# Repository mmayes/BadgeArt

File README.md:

# BadgeArt
Resources for learning how to make PCB badge art

### Element14 text tutorials
* [KiCad 6 - Importing Complex Board Outlines as Vector Graphics](https://community.element14.com/members-area/b/blog/posts/kicad-6---importing-complex-board-outlines-as-vector-graphics)
* [KiCad 6 - Adding Logos and Graphics to a Silkscreen](https://community.element14.com/members-area/b/blog/posts/kicad-6---adding-logos-and-graphics-to-a-silkscreen)
* [KiCad 6 - Importing Complex Board Outlines as Vector Graphics](https://community.element14.com/members-area/b/blog/posts/kicad-6---importing-complex-board-outlines-as-vector-graphics)
* [KiCad 6 - Creating PCB Art and Badges](https://community.element14.com/members-area/b/blog/posts/kicad-6---creating-pcb-art-and-badges)
* [Rosie Learns to Solder](https://community.element14.com/members-area/personalblogs/b/frank-milburn-s-blog/posts/rosie-learns-to-solder)

### Stuart Patterson video tutorials
* [Advanced PCB Graphics with KiCAD 6 and Inkscape](https://www.youtube.com/watch?v=zjnwlTgil4A)
* [Complex Edge Cuts in KiCAD 5.x with Inkscape](https://www.youtube.com/watch?v=rhqlP8CRct0)
* [DIY Rudolph Christmas Tree Ornament](https://www.youtube.com/watch?v=8iXEibNfG_s)

### TwinkleTwinkie tutorials
* [Understanding & Making PCB Art - DEF CON 27 (2019) HHV Talk](https://www.youtube.com/watch?v=Sbkvza8cKQE)
* [PCB Art is Pain](https://www.youtube.com/watch?v=5G-uHDRKI1k)

### Hackster tutorials
* [Design a SAO in KiCad](https://www.youtube.com/watch?v=bXg2j4ttgis)
* [Design a SAO in KiCad](https://www.hackster.io/glowascii/design-a-sh-tty-add-on-in-kicad-06350f)
* [PCB Art Workshop w/Andrew Sowa](https://www.youtube.com/watch?v=-QPkSICzRDk&t=0s)

### Other tutorials/examples
* [Negative Copper Art in KiCad](https://medium.com/the-bkpt/negative-copper-art-in-kicad-d9fae03d9996)
* [Creating Circuit Boards with KiCad 6](https://www.youtube.com/watch?v=5Be7XOMmPQE)
* [A TUTORIAL ON “MAKE NOISE” STYLE INDICATOR LIGHTS AND DESIGNING AN ILLUMINATED BLIND PLATE USING KICAD](https://www.threetom.com/news/a-tutorial-on-make-noise-style-indicator-lights-and-designing-an-illuminated-blind-plate-using-kicad/)
* [SAO PCB Art examples](https://github.com/LifeOnAFarm/SAO-PCB-Art)
* [Drawing PCBs with Inkscape Creating printed circuit board designs using Inkscape, SVG2Shenzhen, and KiCad](https://www.youtube.com/watch?v=xXRPw7ItMaM)
* [Making a PCB Badge for Hackaday Supercon!](https://www.youtube.com/watch?v=YqdBiOj8uXw)
* [A Practical Guide to Designing PCB Art](https://urish.medium.com/a-practical-guide-to-designing-pcb-art-b5aa22926a5c)

### JLPCB tutorials
* [How to generate Gerber and Drill files in KiCad 6](https://support.jlcpcb.com/article/194-how-to-generate-gerber-and-drill-files-in-kicad-6)
* [How to generate the BOM and Centroid file from KiCAD](https://support.jlcpcb.com/article/84-how-to-generate-the-bom-and-centroid-file-from-kicad)
* [KiCad 6 design rules using jlcpcb capabilities](https://www.youtube.com/watch?v=c00A5ZLMKI8)
* [JLCPCB - SMT Assembly with KiCad](https://www.youtube.com/watch?v=VejO8rDdhzo)

### SAO standard info
* [Simple Add-ons (SAO) v2](https://hackaday.io/project/175182-simple-add-ons-sao)
* [SAO v1.69bis standard](https://hackaday.io/project/52950-shitty-add-ons/log/159806-introducing-the-shitty-add-on-v169bis-standard)
* [INTRODUCING THE SHITTY ADD-ON V1.69BIS STANDARD](https://hackaday.com/2019/03/20/introducing-the-shitty-add-on-v1-69bis-standard/)

### Additional libraries/code
* [svg2shenzhen](https://github.com/twinkletwinkie/svg2shenzhen)
* [Inkscape Export Layers](https://github.com/jespino/inkscape-export-layers)
* [bitmap2component](https://github.com/KiCad/kicad-source-mirror/tree/master/bitmap2component)
* [svg2mod](https://github.com/svg2mod/svg2mod)
* [KiCAD JLCPCB tools](https://github.com/Bouni/kicad-jlcpcb-tools)

### Helpful pages for specific issues
* [How to include the canvas in an Inkscape PNG export?](https://graphicdesign.stackexchange.com/questions/137238/how-to-include-the-canvas-in-an-inkscape-png-export)
* [PRINTED CIRCUIT BOARD SURFACE FINISHES: ADVANTAGES AND DISADVANTAGES](https://www.epectec.com/articles/pcb-surface-finish-advantages-and-disadvantages.html)
* [How to Easily Invert Solder Mask Layer Graphics](https://forum.kicad.info/t/how-to-easily-invert-solder-mask-layer-graphics/13383)
* [How can I write text in solder mask?](https://forum.kicad.info/t/how-can-i-write-text-in-solder-mask/11587)
* [Halftone PCB art](http://ianrrees.github.io/2018/06/20/pcb-graphics-with-kicad-+-gimp.html)
* [Removing Solder Mask and Copper Fill YouTube video](https://youtu.be/TmriDK7Jpes)
* [Exporting Gerbers from the Beginner's Guide to KiCAD](https://learn.sparkfun.com/tutorials/beginners-guide-to-kicad/exporting-gerbers)

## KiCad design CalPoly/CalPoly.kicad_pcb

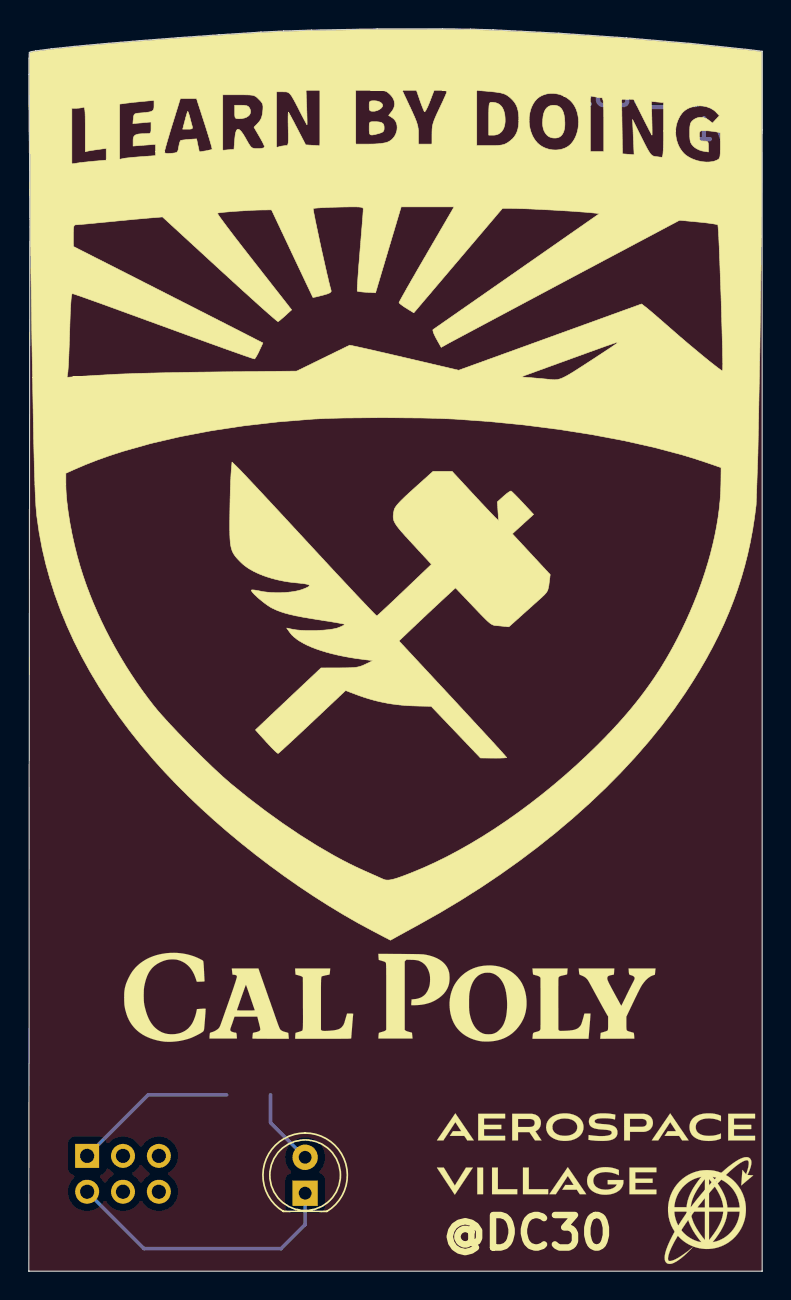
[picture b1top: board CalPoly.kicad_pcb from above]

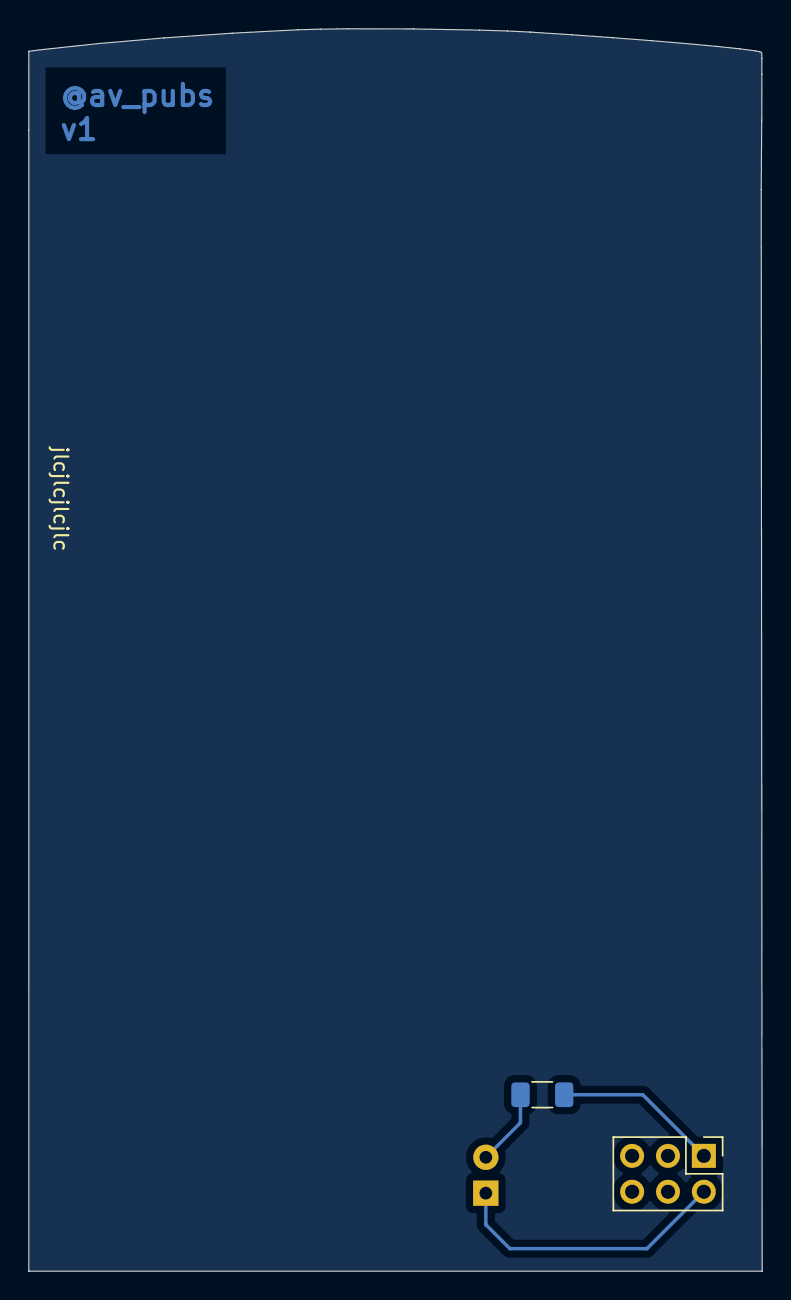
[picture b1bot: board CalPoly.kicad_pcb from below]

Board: 2 copper layers, 51.9 x 88.0 mm, 3 parts (2 on the bottom side), 3 nets.

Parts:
D1: LED; LED_D5.0mm
J1: Conn_02x03_Counter_Clockwise; PinHeader_2x03_P2.54mm_Vertical
R1: R; R_1206_3216Metric_Pad1.30x1.75mm_HandSolder

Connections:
unnamed: D1.2 (A), R1.1
unnamed: D1.1 (K), J1.2
unnamed: J1.1, R1.2

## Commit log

2022-05-04 First commit of links for learning badge art and SAOs
2022-05-04 Added link to github for KiCAD JLCPCB tools
2022-05-25 Added some links to address specific issues
2022-05-25 Added link for details on Halftone PCB Art
2022-07-02 AN225 SAO v1
2022-07-02 v1 of the various B2 SAO configurations
2022-07-02 HAS DC30 SAO v1
2022-07-02 Boeing DC30 SAO v1
2022-07-02 Mooney SAO v1
2022-07-02 Added AN225 SVG images that are computer traced rather than hand traced
2022-07-02 added gitignore file
2022-07-02 reorganize files to match the other kicad SAO folders
2022-07-02 v2 of AN225 SAO that uses a computer traced image for the badge instead of hand drawn
2022-07-16 787 airplane SAO
2022-07-16 787 head-on SAO
2022-07-16 Boeing SAO update to give their logo more space
2022-07-16 DDS SAO update
2022-07-16 poop emoji SAO
2022-07-16 sticker holder SAO
2022-07-16 removed fp-info-cache from repository
2022-07-20 placed 787 source images in their own directory since multiple versions of the 787 SAO reference them
2022-07-20 updates to sticker holder SAO
2022-07-20 updates to Mooney SAO
2022-07-20 added link to youtube video on removing copper fill from an area
2022-07-20 updated HAS SAO with an LED
2022-07-20 updated the Boeing SAO to reflect their logo guidelines and added an LED
2022-07-20 updated the B2 SMD version of the SAO
2022-07-20 created the Council of Matts SAO
2022-07-20 updated AN225 SAO
2022-07-20 updated 787 SAO version without Boeing logo
2022-07-20 update 787 SAO with Boeing logo and LED to reflect logo spacing request
2022-07-20 update 787 SAO with Boeing logo to reflect logo spacing request from Boeing
2022-07-20 Added link to Exporting Gerbers from the Beginner's Guide to KiCAD
2022-07-21 council of matts images added
2022-07-21 safety third image added
2022-07-21 taster of gins images added
2022-07-22 v2 of 787 SAO with Boeing logo
2022-07-22 v2 of B2 SAO
2022-07-22 v3 of Boeing SAO
2022-07-22 Added runway source images that are used in the crew and speaker SAO badges
2022-07-22 Moved KLAS and QR code images over to this repository since they weren't getting used on the AV badge repository
2022-07-28 moved the SMD version of the B2 to the 2022 badge repository
2022-08-02 an225 removed from this repository and moved to the av2022 badge repo
2022-08-02 v1 of the council of matts badges. Created multiple iterations.
2022-08-02 kicad templates for different fabricators
2022-08-02 v4 of Boeing SAO
2022-08-02 v3 of HAS SAO
2022-08-02 v1 of PTP SAO
2022-08-02 v2 of PTP SAO. Attempted to have the non capitalized letters just show as copper
2022-08-02 added ptp logo from twitter
2022-08-02 DDS SAO v1
2022-08-02 AWS v1
2022-08-02 United SAO v1
2022-08-02 Red Balloon SAO v1
2022-08-02 AWS SAO v2
2022-08-02 v2 of United SAO
2022-08-02 v1 of Intelligenesis SAO
2022-08-02 v2 of Intelligenesis SAO
2022-08-02 Cal Poly SAO v1
2022-08-02 SAO template
2022-08-02 v2 Blue Origin SAO
2022-08-02 v3 Blue Origin SAO
2022-08-02 AIAA SAO v1
2022-08-03 captech SAO v1
2022-08-04 CTCubed SAO v1
2022-08-04 taster of gins SAO v1
